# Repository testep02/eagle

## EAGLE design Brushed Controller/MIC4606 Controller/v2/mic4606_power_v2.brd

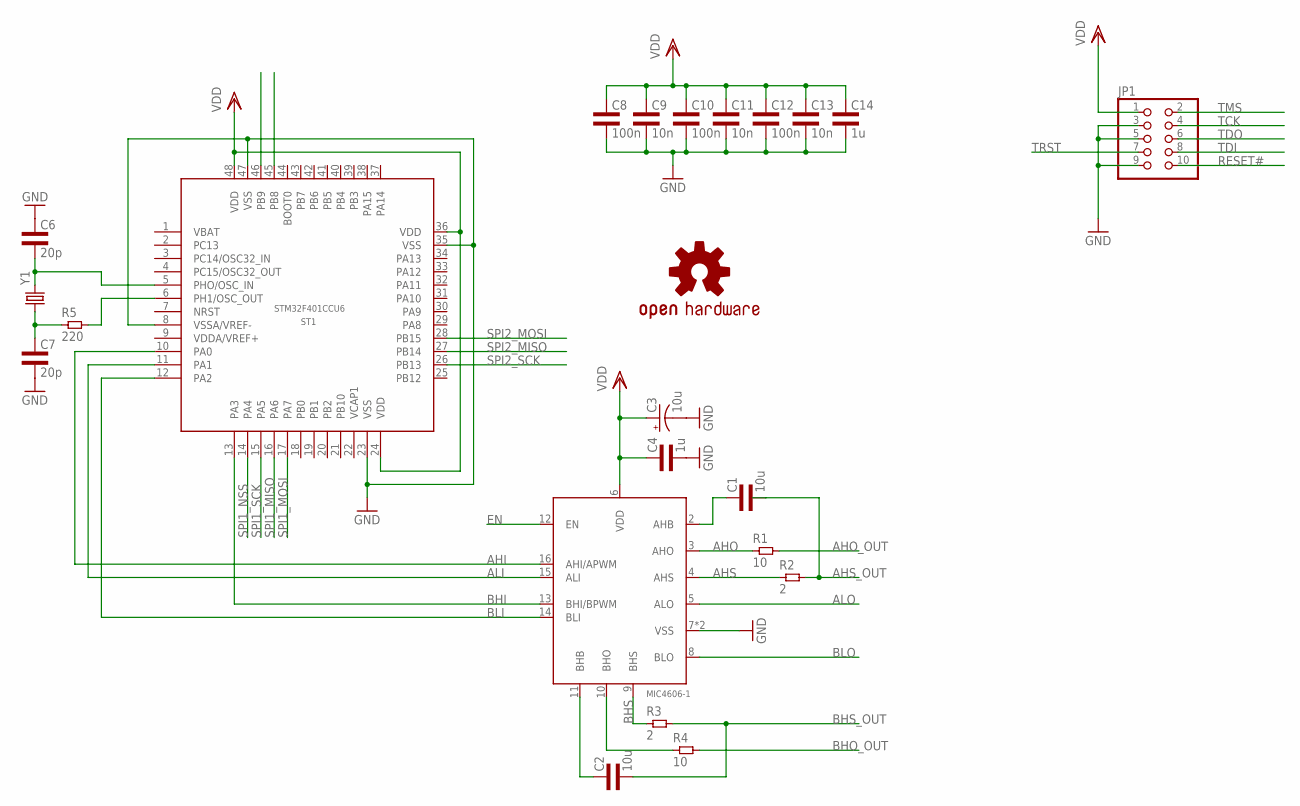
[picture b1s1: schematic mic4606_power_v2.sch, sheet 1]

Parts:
C1, C2: 10u; 0805L3
C3: 10u; E1,8-4
C4: 1u; 0603L3
C6, C7: 20p; 0603L3
C8, C10, C12: 100n; 0603L3
C9, C11, C13: 10n; 0603L3
C14: 1u; 0805L3
JP1: PINHD-2X5; 2X05
LOGO1: OSHW-LOGOM; OSHW-LOGO-M
MD1: MIC4606-1; QFN44-16LD-PL-2
R1, R4: 10; 0805L3
R2, R3: 2; 0805L3
R5: 220; 0603L3
ST1: STM32F401CCU6; UFQFPN48
Y1: CRYSTALHC49US; HC49US

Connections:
AHI: MD1.16 (AHI/APWM), ST1.10 (PA0)
AHO: MD1.3 (AHO), R1.1
AHO_OUT: R1.2
AHS: MD1.4 (AHS), R2.1
AHS_OUT: C1.2, R2.2
ALI: MD1.15 (ALI), ST1.11 (PA1)
ALO: MD1.5 (ALO)
BHI: MD1.13 (BHI/BPWM), ST1.13 (PA3)
BHO: MD1.10 (BHO), R4.1
BHO_OUT: R4.2
BHS: MD1.9 (BHS), R3.1
BHS_OUT: C2.2, R3.2
BLI: MD1.14 (BLI), ST1.12 (PA2)
BLO: MD1.8 (BLO)
CS_G: ST1.45 (PB8); also elsewhere on the board
CS_XM: ST1.46 (PB9); also elsewhere on the board
EN: MD1.12 (EN)
GND: C3.-, C4.P$2 (2), C6.P$1 (1), C7.P$2 (2), C8.P$2 (2), C9.P$2 (2), C10.P$2 (2), C11.P$2 (2), C12.P$2 (2), C13.P$2 (2), C14.2, JP1.3, JP1.5, JP1.9, MD1.7 (VSS), MD1.TP (VSS), ST1.8 (VSSA/VREF-), ST1.23 (VSS), ST1.35 (VSS), ST1.47 (VSS); also elsewhere on the board
unnamed: C1.1, MD1.2 (AHB)
unnamed: R5.P$2 (2), ST1.6 (PH1/OSC_OUT)
unnamed: C7.P$1 (1), R5.P$1 (1), Y1.1
unnamed: C2.1, MD1.11 (BHB)
unnamed: C6.P$2 (2), ST1.5 (PHO/OSC_IN), Y1.2
RESET#: JP1.10
SPI1_MISO: ST1.16 (PA6); also elsewhere on the board
SPI1_MOSI: ST1.17 (PA7); also elsewhere on the board
SPI1_NSS: ST1.14 (PA4); also elsewhere on the board
SPI1_SCK: ST1.15 (PA5); also elsewhere on the board
SPI2_MISO: ST1.27 (PB14); also elsewhere on the board
SPI2_MOSI: ST1.28 (PB15); also elsewhere on the board
SPI2_SCK: ST1.26 (PB13); also elsewhere on the board
TCK: JP1.4
TDI: JP1.8
TDO: JP1.6
TMS: JP1.2
TRST: JP1.7
VDD: C3.+, C4.P$1 (1), C8.P$1 (1), C9.P$1 (1), C10.P$1 (1), C11.P$1 (1), C12.P$1 (1), C13.P$1 (1), C14.1, JP1.1, MD1.6 (VDD), ST1.24 (VDD), ST1.36 (VDD), ST1.48 (VDD); also elsewhere on the board

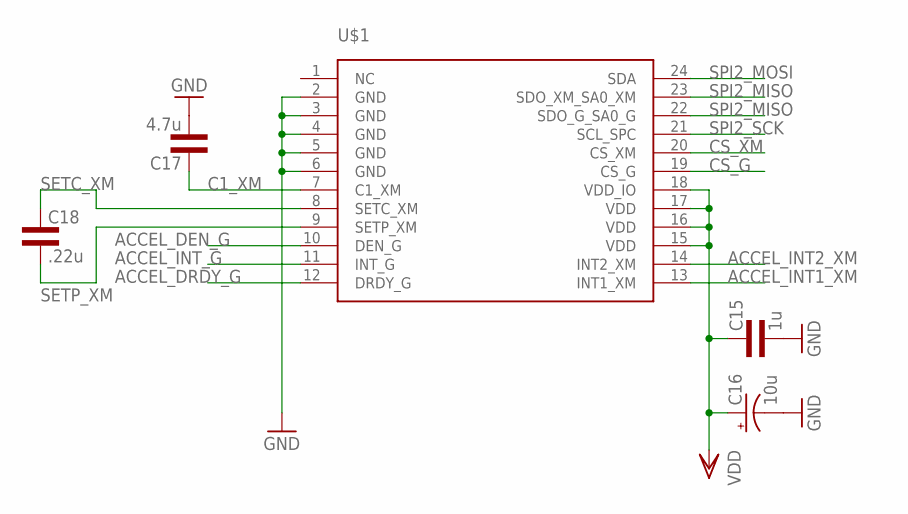
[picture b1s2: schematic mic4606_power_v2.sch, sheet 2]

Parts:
C15: 1u; 0805L3
C16: 10u; CT3216
C17: 4.7u; 0603L3
C18: .22u; 0603L3
U$1: ST_LSM9DS0_TEMP_SENSE_LSM9DS0; ST_LSM9DS0_TEMP_SENSE_LGA-24

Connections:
ACCEL_DEN_G: U$1.10 (DEN_G)
ACCEL_DRDY_G: U$1.12 (DRDY_G)
ACCEL_INT1_XM: U$1.13 (INT1_XM)
ACCEL_INT2_XM: U$1.14 (INT2_XM)
ACCEL_INT_G: U$1.11 (INT_G)
C1_XM: C17.P$1 (1), U$1.7 (C1_XM)
CS_G: U$1.19 (CS_G); also elsewhere on the board
CS_XM: U$1.20 (CS_XM); also elsewhere on the board
GND: C15.2, C16.-, C17.P$2 (2), U$1.2 (GND), U$1.3 (GND), U$1.4 (GND), U$1.5 (GND), U$1.6 (GND); also elsewhere on the board
SETC_XM: C18.P$1 (1), U$1.8 (SETC_XM)
SETP_XM: C18.P$2 (2), U$1.9 (SETP_XM)
SPI2_MISO: U$1.22 (SDO_G_SA0_G), U$1.23 (SDO_XM_SA0_XM); also elsewhere on the board
SPI2_MOSI: U$1.24 (SDA); also elsewhere on the board
SPI2_SCK: U$1.21 (SCL_SPC); also elsewhere on the board
VDD: C15.1, C16.+, U$1.15 (VDD), U$1.16 (VDD), U$1.17 (VDD), U$1.18 (VDD_IO); also elsewhere on the board

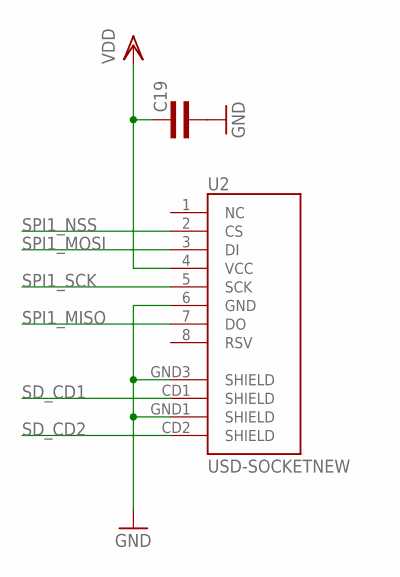
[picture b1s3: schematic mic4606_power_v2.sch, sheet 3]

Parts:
C19: CAP0603L3; 0603L3
U2: USD-SOCKETNEW; MICRO-SD-SOCKET-PP

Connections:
GND: C19.P$2 (2), U2.6 (GND), U2.GND1 (SHIELD), U2.GND3 (SHIELD); also elsewhere on the board
SD_CD1: U2.CD1 (SHIELD)
SD_CD2: U2.CD2 (SHIELD)
SPI1_MISO: U2.7 (DO); also elsewhere on the board
SPI1_MOSI: U2.3 (DI); also elsewhere on the board
SPI1_NSS: U2.2 (CS); also elsewhere on the board
SPI1_SCK: U2.5 (SCK); also elsewhere on the board
VDD: C19.P$1 (1), U2.4 (VCC); also elsewhere on the board

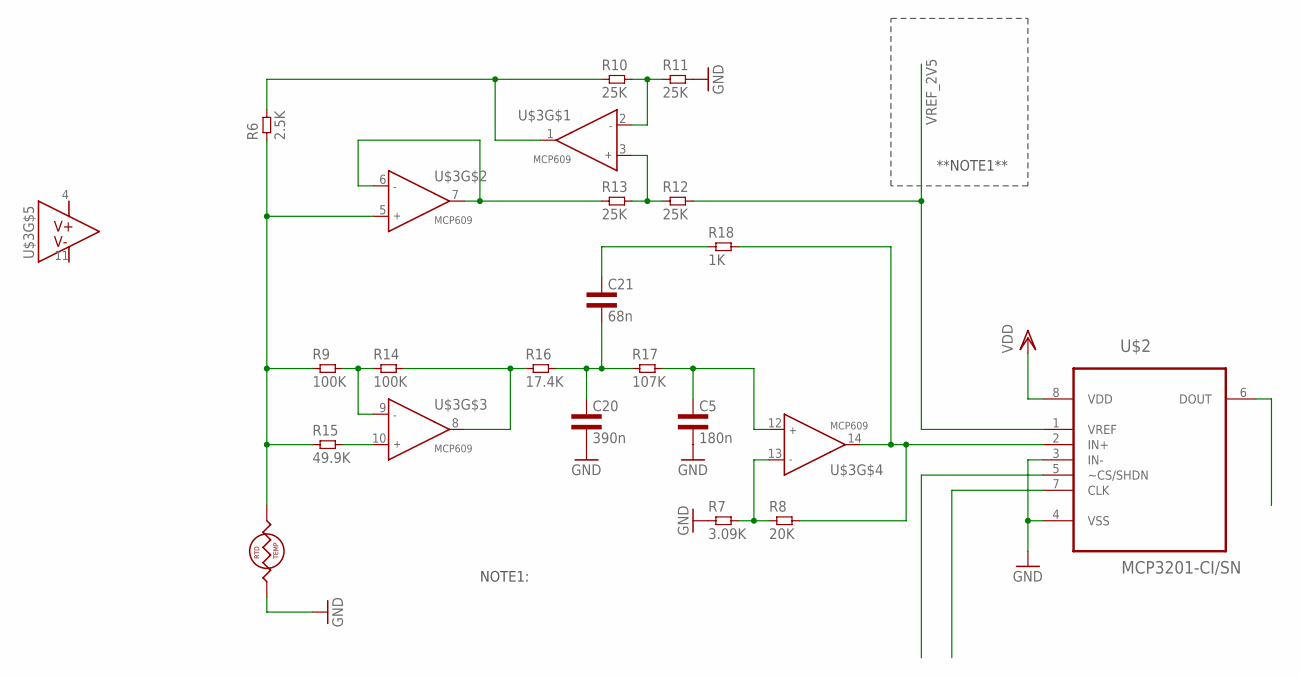
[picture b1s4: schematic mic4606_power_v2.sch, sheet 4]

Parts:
C5: 180n; 0603L3
C20: 390n; 0603L3
C21: 68n; 0603L3
R6: 2.5K; 0603L3
R7: 3.09K; 0603L3
R8: 20K; 0603L3
R9, R14: 100K; 0603L3
R10, R11, R12, R13: 25K; 0603L3
R15: 49.9K; 0603L3
R16: 17.4K; 0603L3
R17: 107K; 0603L3
R18: 1K; 0603L3
RTD1: RTD0805L1; 0805L1
U$2: MCP3201-CI/SN; SOIC127P600X175-8N
U$3: MCP609; TSSOP-14

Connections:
GND: C5.P$2 (2), C20.P$2 (2), R7.P$1 (1), R11.P$2 (2), RTD1.1, U$2.3 (IN-), U$2.4 (VSS); also elsewhere on the board
unnamed: R12.P$1 (1), R13.P$2 (2), U$3.3 (INA+)
unnamed: R10.P$2 (2), R11.P$1 (1), U$3.2 (INA-)
unnamed: R13.P$1 (1), U$3.6 (INA-), U$3.7 (OUTA)
unnamed: R8.P$2 (2), R18.P$2 (2), U$2.2 (IN+), U$3.14 (OUTA)
unnamed: R6.P$2 (2), R10.P$1 (1), U$3.1 (OUTA)
unnamed: R6.P$1 (1), R9.P$1 (1), R15.P$1 (1), RTD1.2, U$3.5 (INA+)
unnamed: R7.P$2 (2), R8.P$1 (1), U$3.13 (INA-)
unnamed: R9.P$2 (2), R14.P$1 (1), U$3.9 (INA-)
unnamed: R15.P$2 (2), U$3.10 (INA+)
unnamed: R14.P$2 (2), R16.P$1 (1), U$3.8 (OUTA)
unnamed: C20.P$1 (1), C21.P$2 (2), R16.P$2 (2), R17.P$1 (1)
unnamed: C5.P$1 (1), R17.P$2 (2), U$3.12 (INA+)
unnamed: C21.P$1 (1), R18.P$1 (1)
V+: U$3.4 (V+)
V-: U$3.11 (V-)
VDD: U$2.8 (VDD); also elsewhere on the board
VREF_2V5: R12.P$2 (2), U$2.1 (VREF)

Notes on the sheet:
**NOTE1**
NOTE1:

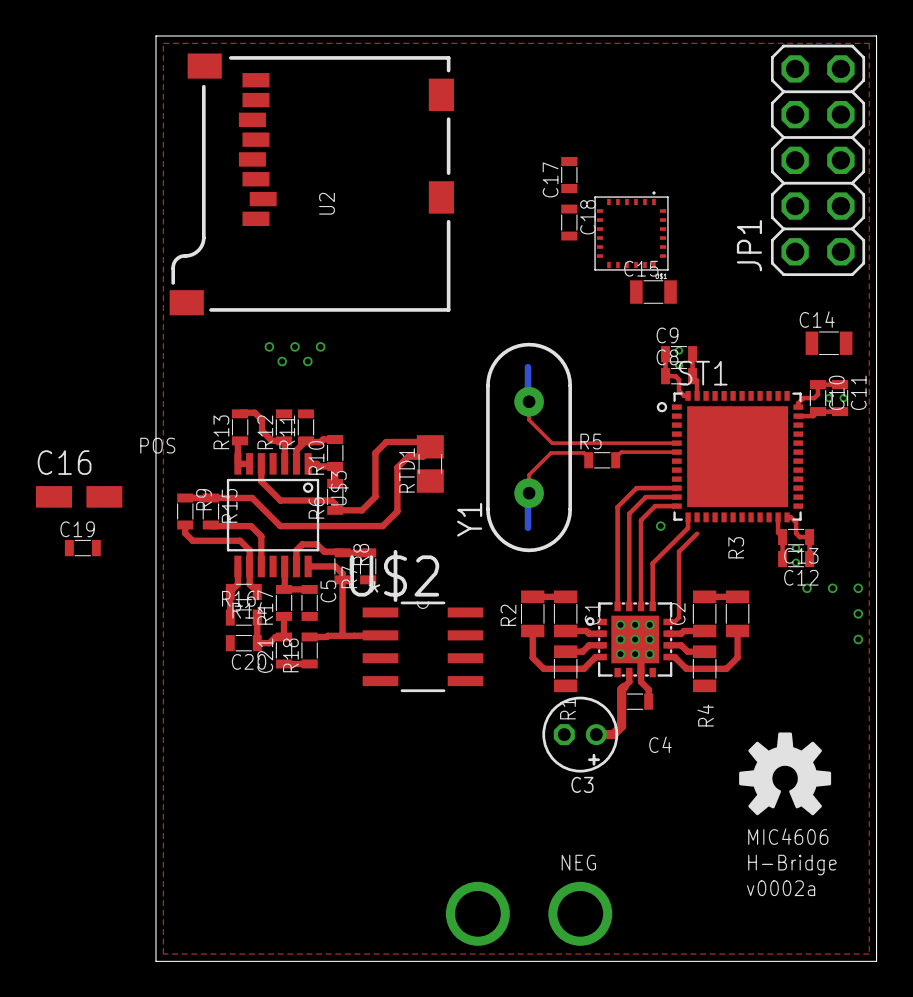
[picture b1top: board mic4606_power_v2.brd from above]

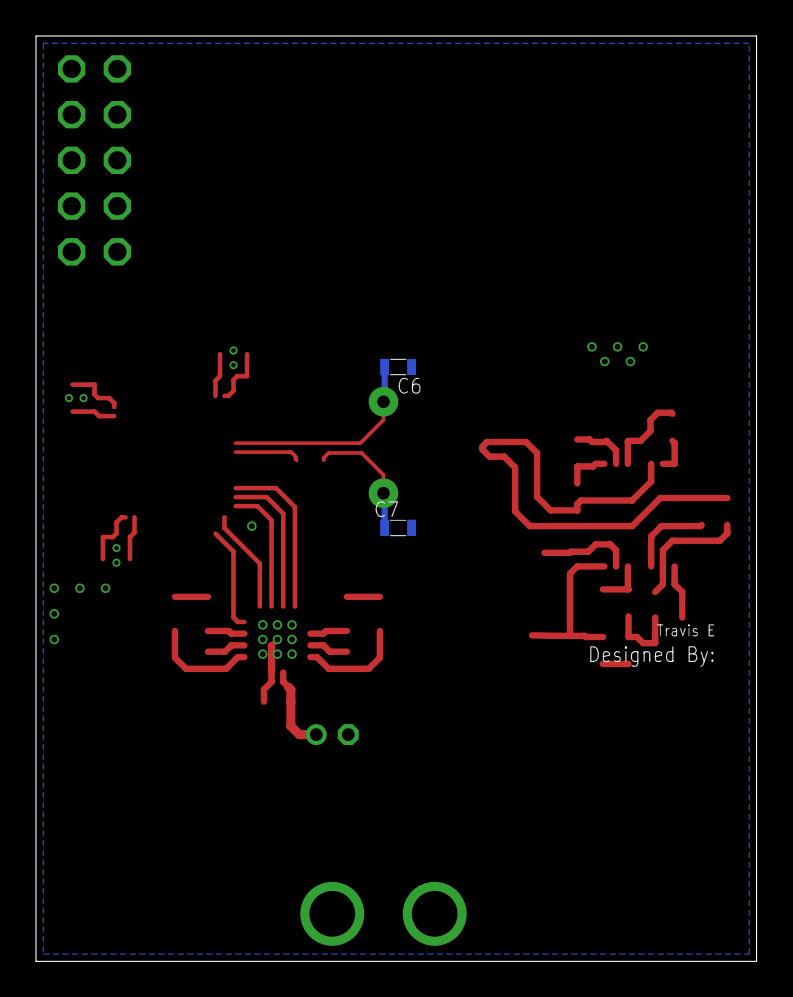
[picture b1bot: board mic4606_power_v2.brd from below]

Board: 2 copper layers, 40.0 x 51.4 mm, 49 parts (2 on the bottom side), 43 nets.

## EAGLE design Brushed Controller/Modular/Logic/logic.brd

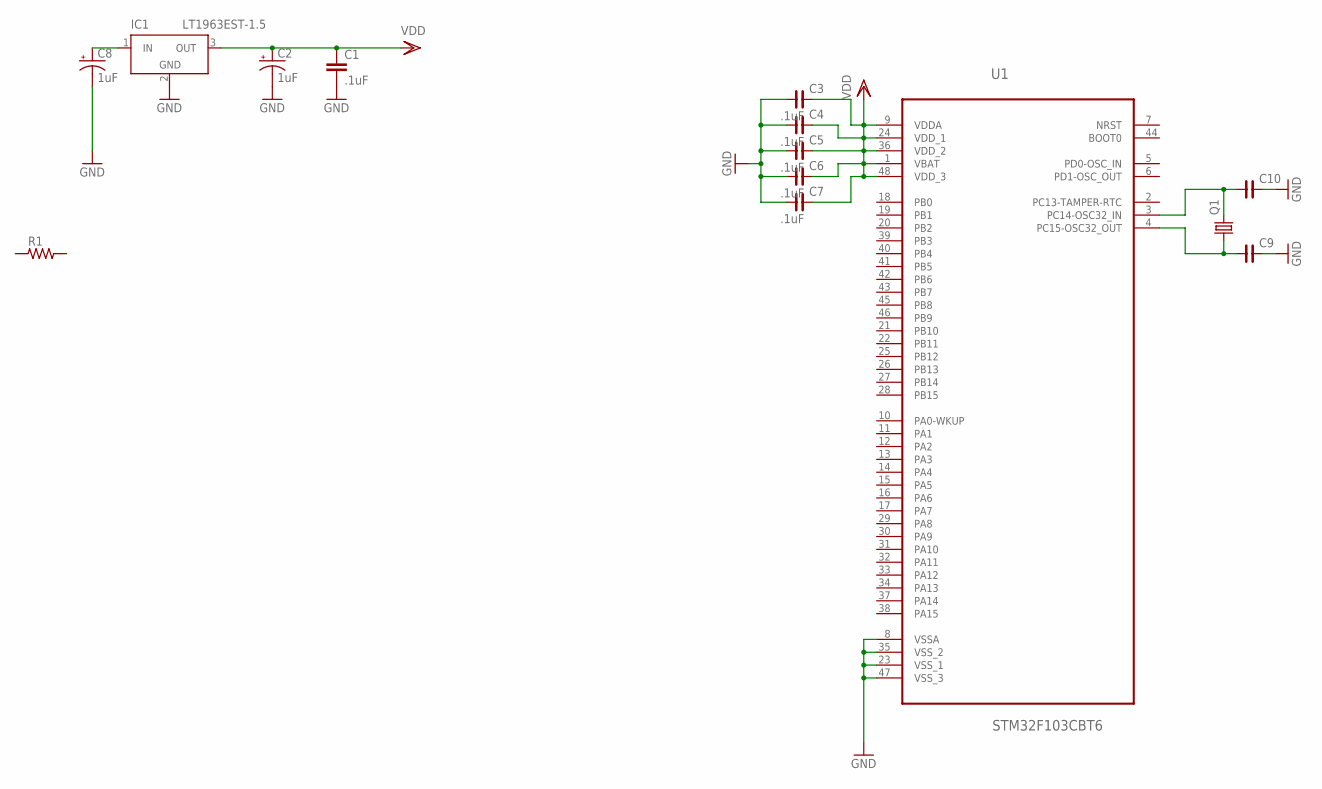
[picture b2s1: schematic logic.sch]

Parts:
C1: .1uF; C0603
C2, C8: 1uF; D/7343-31R
C3, C4, C5, C6, C7: .1uF; C0402
C9, C10: C_0402; C0402
IC1: LT1963EST-1.5; SOT223
Q1: CRYSTALTC26H; TC26H
R1: R_0402; R0402
U1: STM32F103CBT6; QFP50P900X900X160-48N

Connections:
GND: C1.2, C2.-, C3.1, C4.1, C5.1, C6.1, C7.1, C8.-, C9.2, C10.2, IC1.2 (GND), IC1.4 (GND), U1.8 (VSSA), U1.23 (VSS_1), U1.35 (VSS_2), U1.47 (VSS_3)
unnamed: C10.1, Q1.2, U1.3 (PC14-OSC32_IN)
unnamed: C9.1, Q1.1, U1.4 (PC15-OSC32_OUT)
unnamed: C8.+, IC1.1 (IN)
PA11: U1.32 (PA11)
VDD: C1.1, C2.+, C3.2, C4.2, C5.2, C6.2, C7.2, IC1.3 (OUT), U1.1 (VBAT), U1.9 (VDDA), U1.24 (VDD_1), U1.36 (VDD_2), U1.48 (VDD_3)

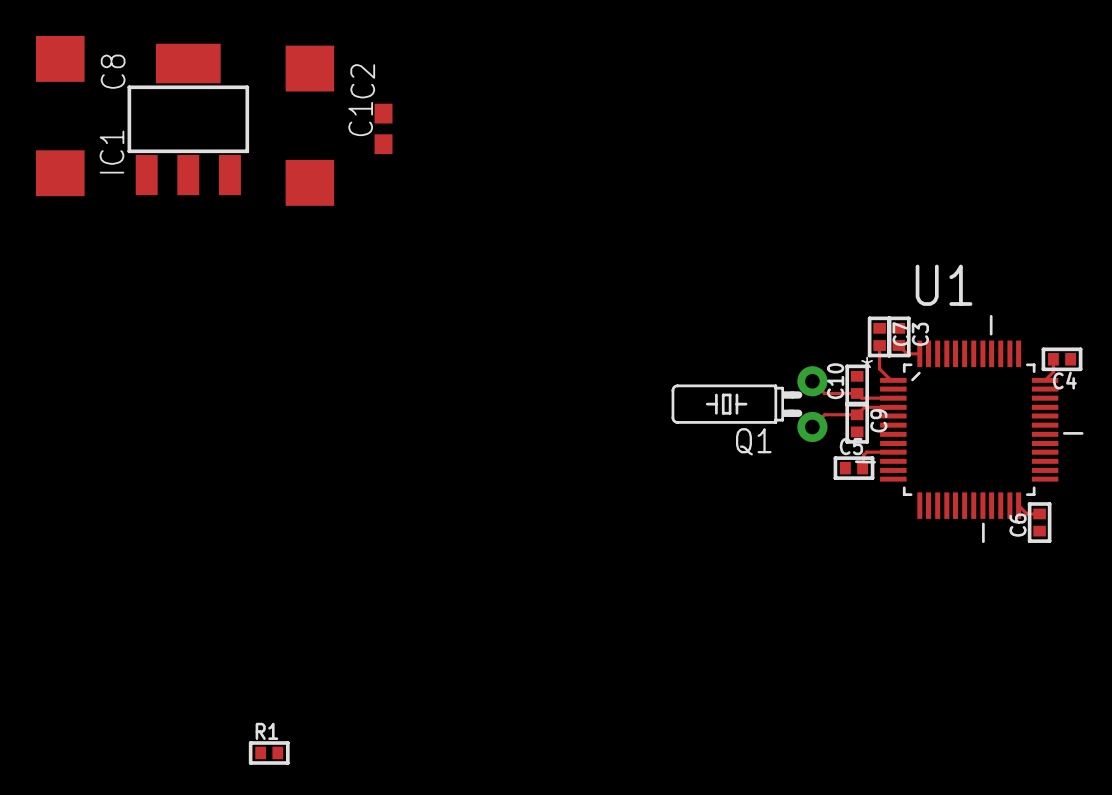
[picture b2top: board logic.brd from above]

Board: 2 copper layers, 14 parts (0 on the bottom side), 5 nets.

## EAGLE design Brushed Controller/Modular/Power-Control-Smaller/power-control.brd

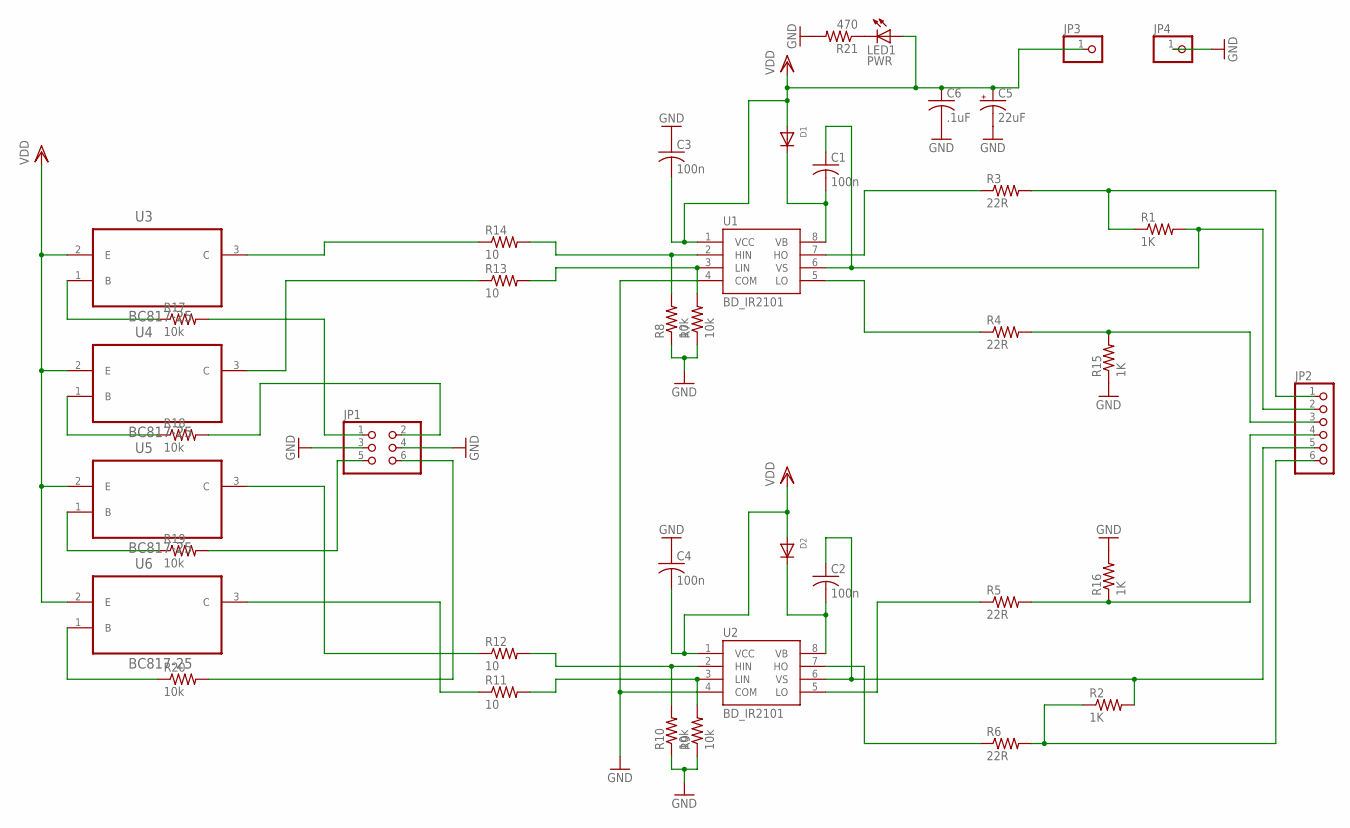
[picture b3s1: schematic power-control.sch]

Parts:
C1, C2, C3, C4: 100n; C0402
C5: 22uF; B/3528-21W
C6: .1uF; C0805
D1, D2: DIODESOD-523; SOD-523
JP1: PINHD-2X3; 2X03
JP2: PINHD-1X6; 1X06
JP3, JP4: PINHD-1X1; 1X01
LED1: PWR; CHIP-LED0805
R1, R2, R15, R16: 1K; R0201
R3, R4, R5, R6: 22R; R0201
R7, R8, R9, R10, R17, R18, R19, R20: 10k; R0201
R11, R12, R13, R14: 10; R0201
R21: 470; R0201
U1, U2: BD_IR2101; SO8
U3, U4, U5, U6: BC817-25; SOT95P240X97-3N

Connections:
GND: C3.1, C4.1, C5.-, C6.2, JP1.3, JP1.4, JP4.1, R7.1, R8.1, R9.1, R10.1, R15.1, R16.2, R21.2, U1.4 (COM), U2.4 (COM)
HO_1: R3.1, U1.7 (HO)
HO_2: R6.1, U2.7 (HO)
LO_1: R4.1, U1.5 (LO)
LO_2: R5.1, U2.5 (LO)
MOTOR_OUT_1: C1.1, JP2.2, R1.2, U1.6 (VS)
MOTOR_OUT_2: C2.1, JP2.5, R2.2, U2.6 (VS)
unnamed: R13.1, U4.3 (C)
unnamed: R11.1, U6.3 (C)
unnamed: R8.2, R14.2, U1.2 (HIN)
unnamed: R7.2, R13.2, U1.3 (LIN)
unnamed: R10.2, R12.2, U2.2 (HIN)
unnamed: R9.2, R11.2, U2.3 (LIN)
unnamed: C1.2, D1.K (C), U1.8 (VB)
unnamed: C2.2, D2.K (C), U2.8 (VB)
unnamed: R12.1, U5.3 (C)
unnamed: JP2.4, R5.2, R16.1
unnamed: R14.1, U3.3 (C)
unnamed: JP1.1, R17.2
unnamed: JP1.5, R19.2
unnamed: JP1.2, R18.2
unnamed: JP2.1, R1.1, R3.2
unnamed: JP1.6, R20.2
unnamed: R17.1, U3.1 (B)
unnamed: R18.1, U4.1 (B)
unnamed: R19.1, U5.1 (B)
unnamed: JP2.3, R4.2, R15.2
unnamed: R20.1, U6.1 (B)
unnamed: LED1.C, R21.1
unnamed: JP2.6, R2.1, R6.2
VDD: C3.2, C4.2, C5.+, C6.1, D1.A, D2.A, JP3.1, LED1.A, U1.1 (VCC), U2.1 (VCC), U3.2 (E), U4.2 (E), U5.2 (E), U6.2 (E)

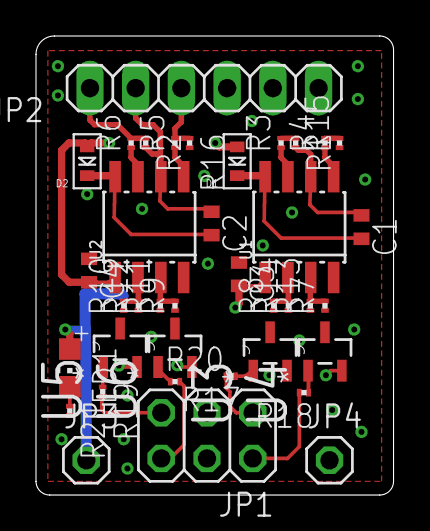
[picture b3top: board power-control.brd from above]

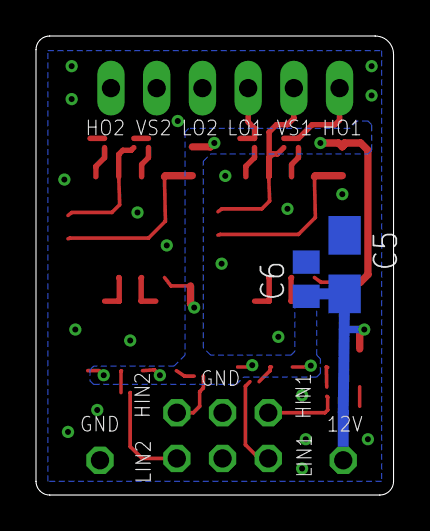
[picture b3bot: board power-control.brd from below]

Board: 2 copper layers, 19.9 x 25.5 mm, 40 parts (2 on the bottom side), 31 nets.

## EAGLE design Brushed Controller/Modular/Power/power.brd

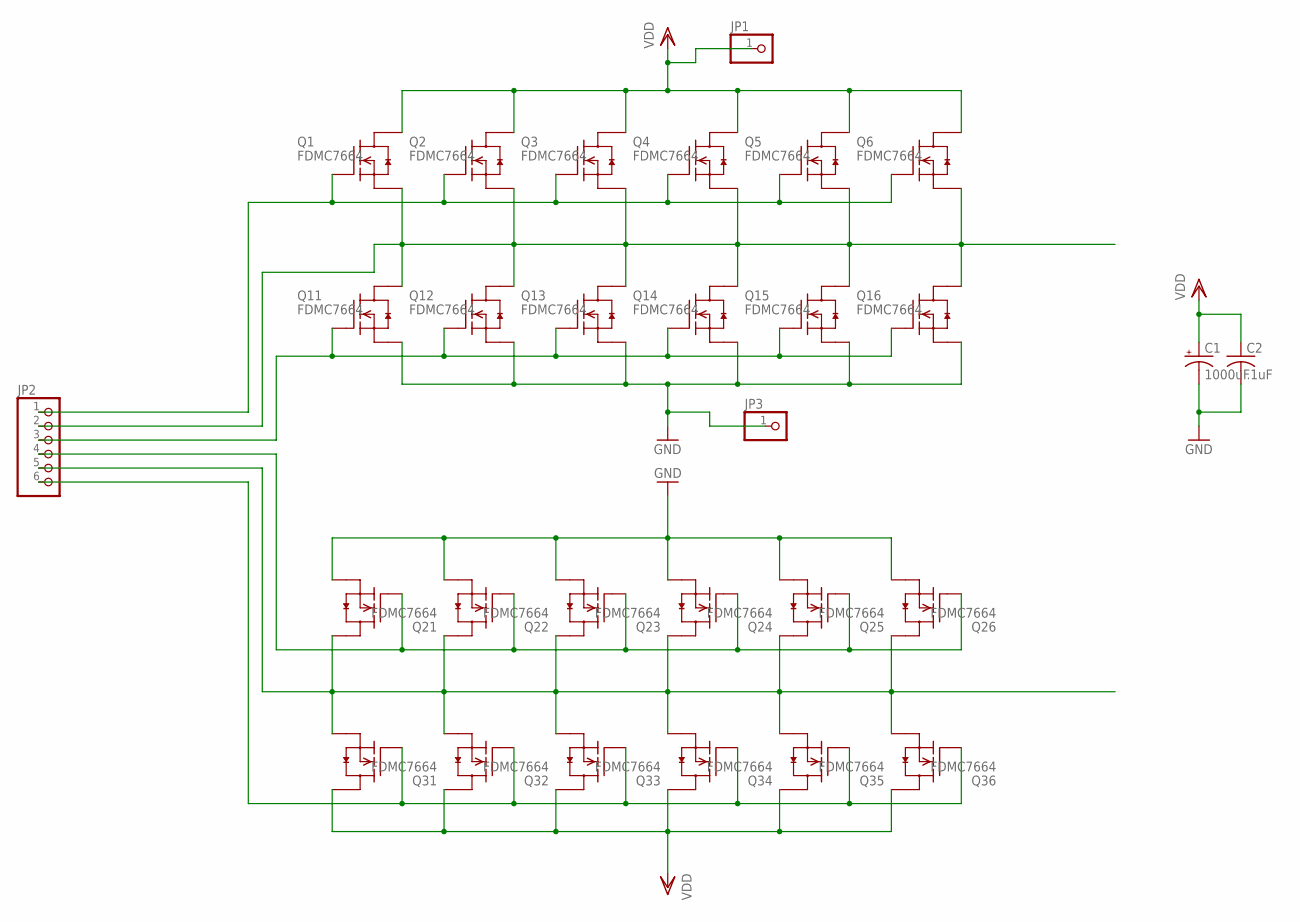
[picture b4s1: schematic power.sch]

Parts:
C1: 1000uF; 140CLH-0810
C2: .1uF; C0603
JP1, JP3: PINHD-1X1; 1X01
JP2: PINHD-1X6; 1X06
Q1, Q2, Q3, Q4, Q5, Q6, Q11, Q12, Q13, Q14, Q15, Q16, Q21, Q22, Q23, Q24, Q25, Q26, Q31, Q32, Q33, Q34, Q35, Q36: FDMC7664; MLP33

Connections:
GND: C1.-, C2.2, JP3.1, Q11.123S (S), Q12.123S (S), Q13.123S (S), Q14.123S (S), Q15.123S (S), Q16.123S (S), Q21.123S (S), Q22.123S (S), Q23.123S (S), Q24.123S (S), Q25.123S (S), Q26.123S (S)
HO_1: JP2.1, Q1.4G (G), Q2.4G (G), Q3.4G (G), Q4.4G (G), Q5.4G (G), Q6.4G (G)
HO_2: JP2.6, Q31.4G (G), Q32.4G (G), Q33.4G (G), Q34.4G (G), Q35.4G (G), Q36.4G (G)
LO_1: JP2.3, Q11.4G (G), Q12.4G (G), Q13.4G (G), Q14.4G (G), Q15.4G (G), Q16.4G (G)
LO_2: JP2.4, Q21.4G (G), Q22.4G (G), Q23.4G (G), Q24.4G (G), Q25.4G (G), Q26.4G (G)
MOTOR_OUT_1: JP2.2, Q1.123S (S), Q2.123S (S), Q3.123S (S), Q4.123S (S), Q5.123S (S), Q6.123S (S), Q11.5678D (D), Q12.5678D (D), Q13.5678D (D), Q14.5678D (D), Q15.5678D (D), Q16.5678D (D)
MOTOR_OUT_2: JP2.5, Q21.5678D (D), Q22.5678D (D), Q23.5678D (D), Q24.5678D (D), Q25.5678D (D), Q26.5678D (D), Q31.123S (S), Q32.123S (S), Q33.123S (S), Q34.123S (S), Q35.123S (S), Q36.123S (S)
VDD: C1.+, C2.1, JP1.1, Q1.5678D (D), Q2.5678D (D), Q3.5678D (D), Q4.5678D (D), Q5.5678D (D), Q6.5678D (D), Q31.5678D (D), Q32.5678D (D), Q33.5678D (D), Q34.5678D (D), Q35.5678D (D), Q36.5678D (D)

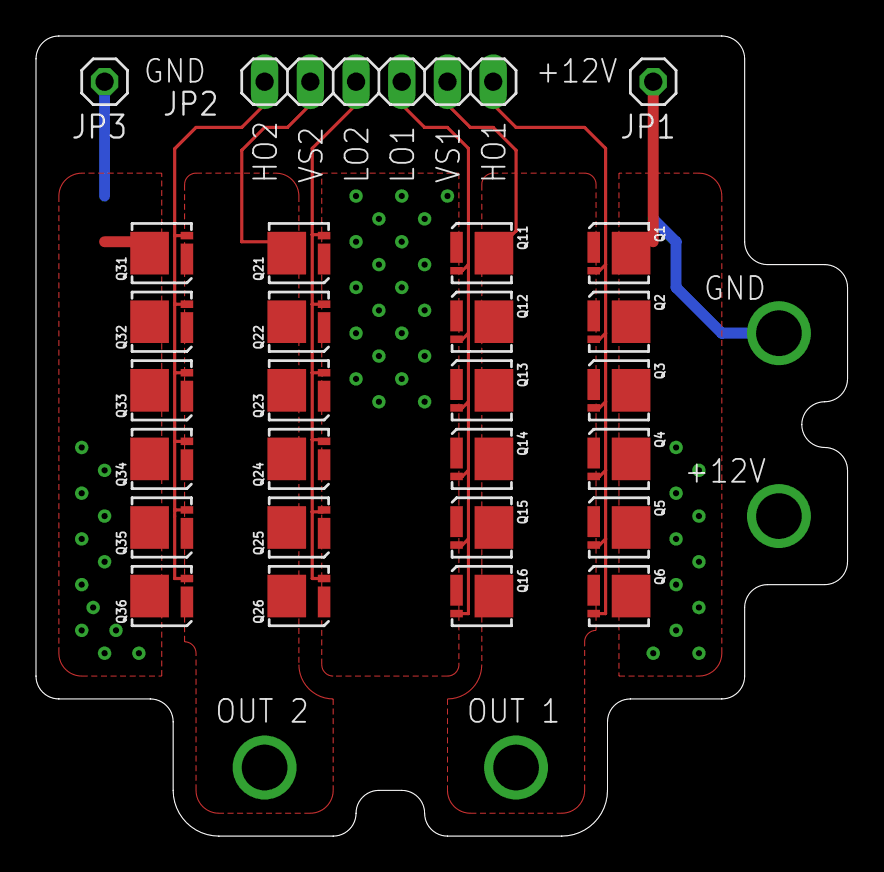
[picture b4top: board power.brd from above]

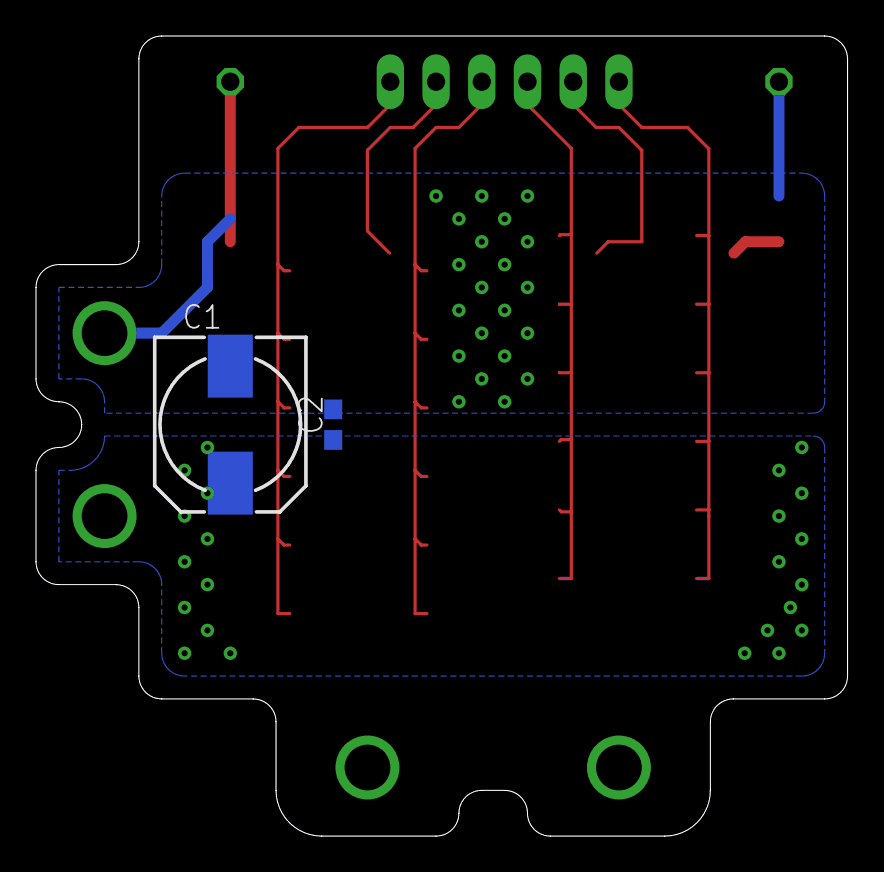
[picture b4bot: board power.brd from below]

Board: 2 copper layers, 45.1 x 44.4 mm, 29 parts (2 on the bottom side), 8 nets.

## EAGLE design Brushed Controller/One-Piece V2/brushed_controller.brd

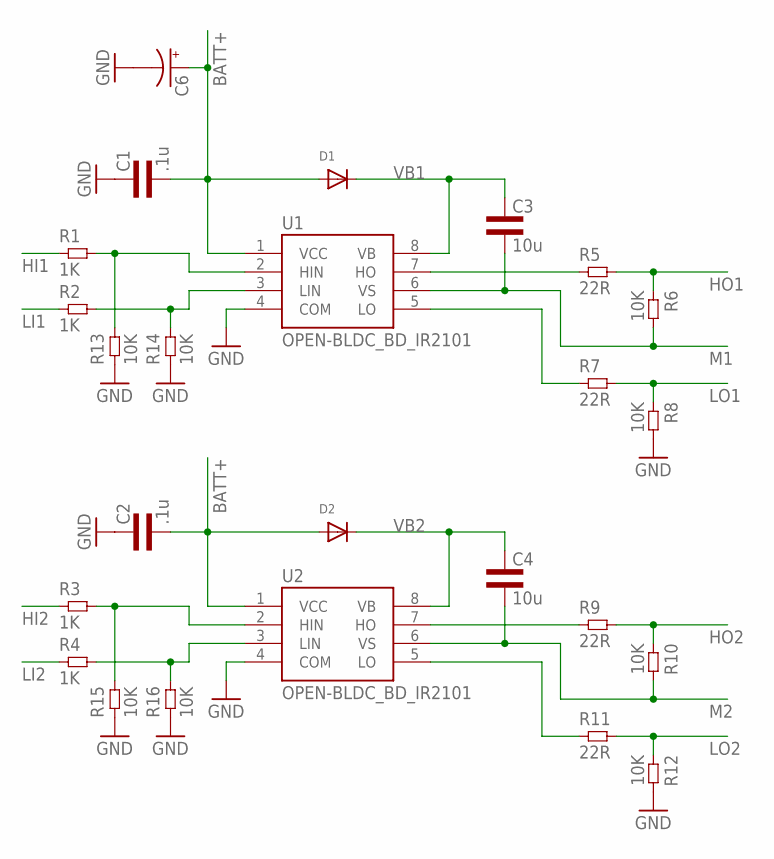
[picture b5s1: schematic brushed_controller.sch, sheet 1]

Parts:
C1, C2: .1u; 0603L3
C3, C4: 10u; 0805L3
C6: CPOL-USCT7343; CT7343
D1, D2: DIODESOD-523; SOD-523
R1, R2, R3, R4: 1K; 0603L3
R5, R7, R9, R11: 22R; 0805L3
R6, R8, R10, R12: 10K; 0805L3
R13, R14, R15, R16: 10K; 0603L3
U1, U2: OPEN-BLDC_BD_IR2101; OPEN-BLDC_SO8

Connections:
BATT+: C1.P$2 (2), C2.P$2 (2), C6.+, D1.A, D2.A, U1.1 (VCC), U2.1 (VCC); also elsewhere on the board
GND: C1.P$1 (1), C2.P$1 (1), C6.-, R8.2, R12.2, R13.P$1 (1), R14.P$1 (1), R15.P$1 (1), R16.P$1 (1), U1.4 (COM), U2.4 (COM); also elsewhere on the board
H1: R5.1, U1.7 (HO)
H2: R9.1, U2.7 (HO)
HI1: R1.P$1 (1)
HI2: R3.P$1 (1)
HO1: R5.2, R6.1; also elsewhere on the board
HO2: R9.2, R10.1
L1: R7.1, U1.5 (LO)
L2: R11.1, U2.5 (LO)
LI1: R2.P$1 (1)
LI2: R4.P$1 (1)
LO1: R7.2, R8.1; also elsewhere on the board
LO2: R11.2, R12.1; also elsewhere on the board
M1: C3.2, R6.2, U1.6 (VS); also elsewhere on the board
M2: C4.2, R10.2, U2.6 (VS); also elsewhere on the board
unnamed: R1.P$2 (2), R13.P$2 (2), U1.2 (HIN)
unnamed: R2.P$2 (2), R14.P$2 (2), U1.3 (LIN)
unnamed: R3.P$2 (2), R15.P$2 (2), U2.2 (HIN)
unnamed: R4.P$2 (2), R16.P$2 (2), U2.3 (LIN)
VB1: C3.1, D1.K (C), U1.8 (VB)
VB2: C4.1, D2.K (C), U2.8 (VB)

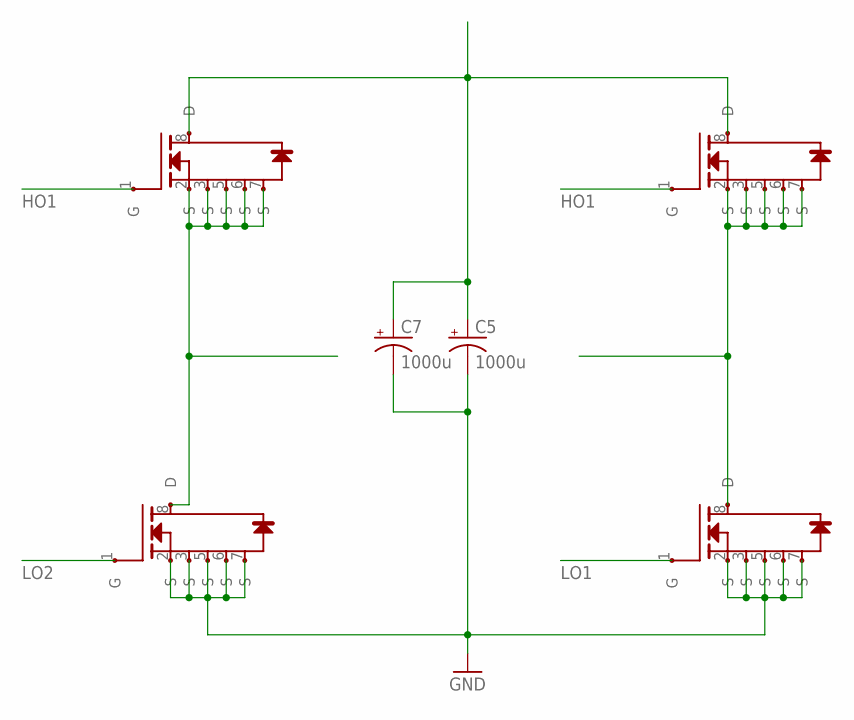
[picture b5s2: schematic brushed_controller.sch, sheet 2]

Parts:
C5, C7: 1000u; E5-13
U$1, U$2, U$3, U$4: IR-MOSFETS_IRF3805STRL-7PP; IR-MOSFETS_D2PAK-7

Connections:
BATT+: C5.+, C7.+, U$1.8 (D), U$3.8 (D); also elsewhere on the board
GND: C5.-, C7.-, U$2.2 (S), U$2.3 (S), U$2.5 (S), U$2.6 (S), U$2.7 (S), U$4.2 (S), U$4.3 (S), U$4.5 (S), U$4.6 (S), U$4.7 (S); also elsewhere on the board
HO1: U$1.1 (G), U$3.1 (G); also elsewhere on the board
LO1: U$4.1 (G); also elsewhere on the board
LO2: U$2.1 (G); also elsewhere on the board
M1: U$1.2 (S), U$1.3 (S), U$1.5 (S), U$1.6 (S), U$1.7 (S), U$2.8 (D); also elsewhere on the board
M2: U$3.2 (S), U$3.3 (S), U$3.5 (S), U$3.6 (S), U$3.7 (S), U$4.8 (D); also elsewhere on the board

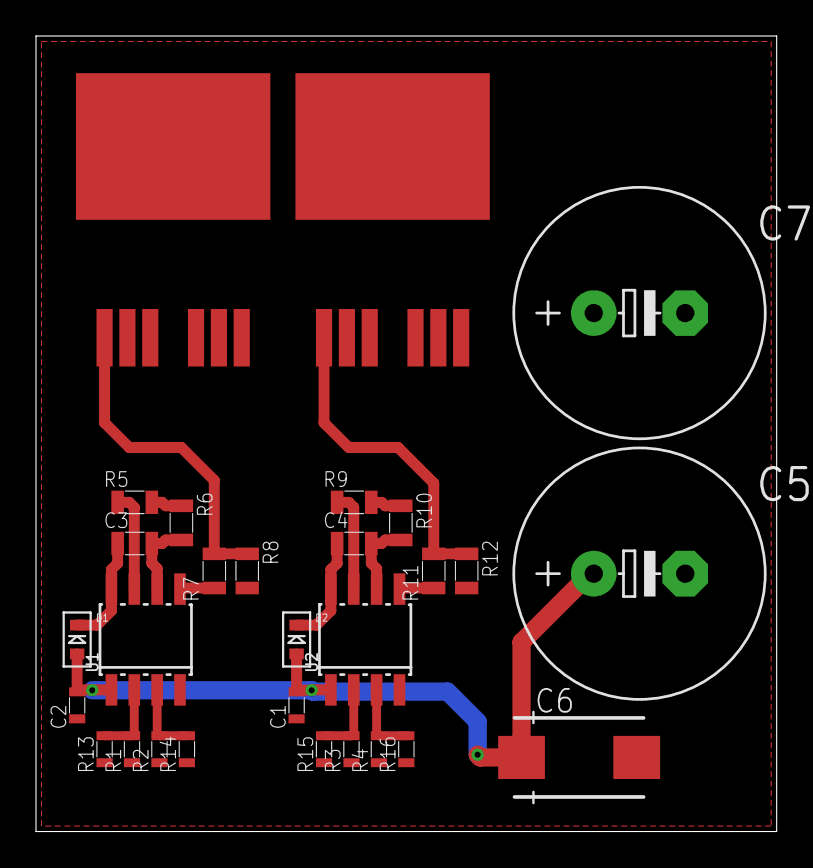
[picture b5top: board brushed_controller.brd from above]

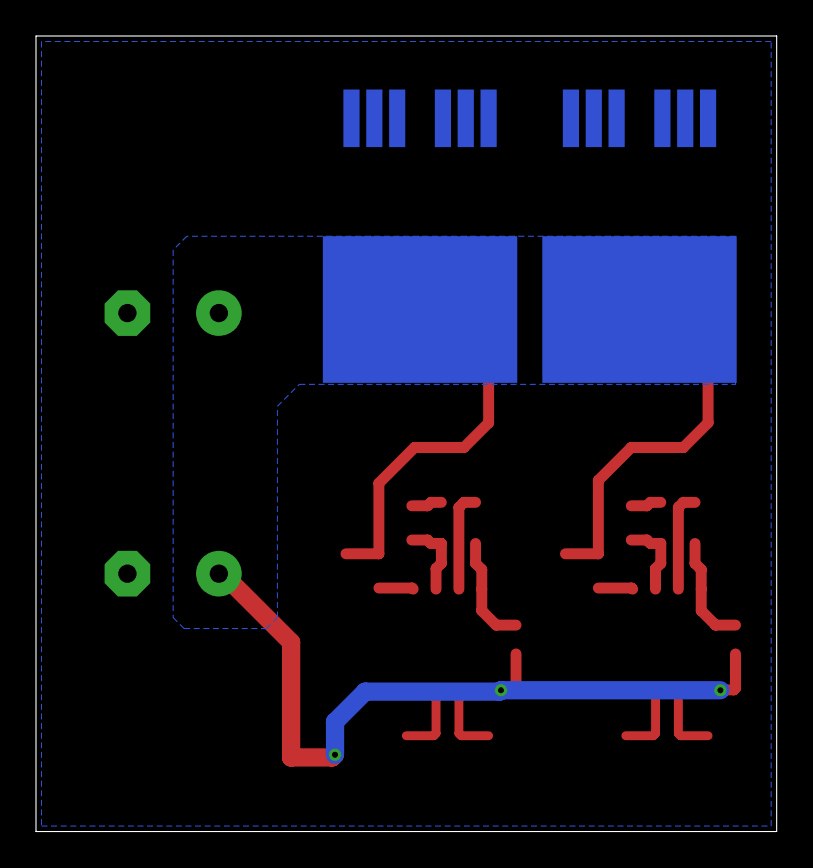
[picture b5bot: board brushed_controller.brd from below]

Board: 2 copper layers, 41.1 x 44.2 mm, 31 parts (2 on the bottom side), 18 nets.

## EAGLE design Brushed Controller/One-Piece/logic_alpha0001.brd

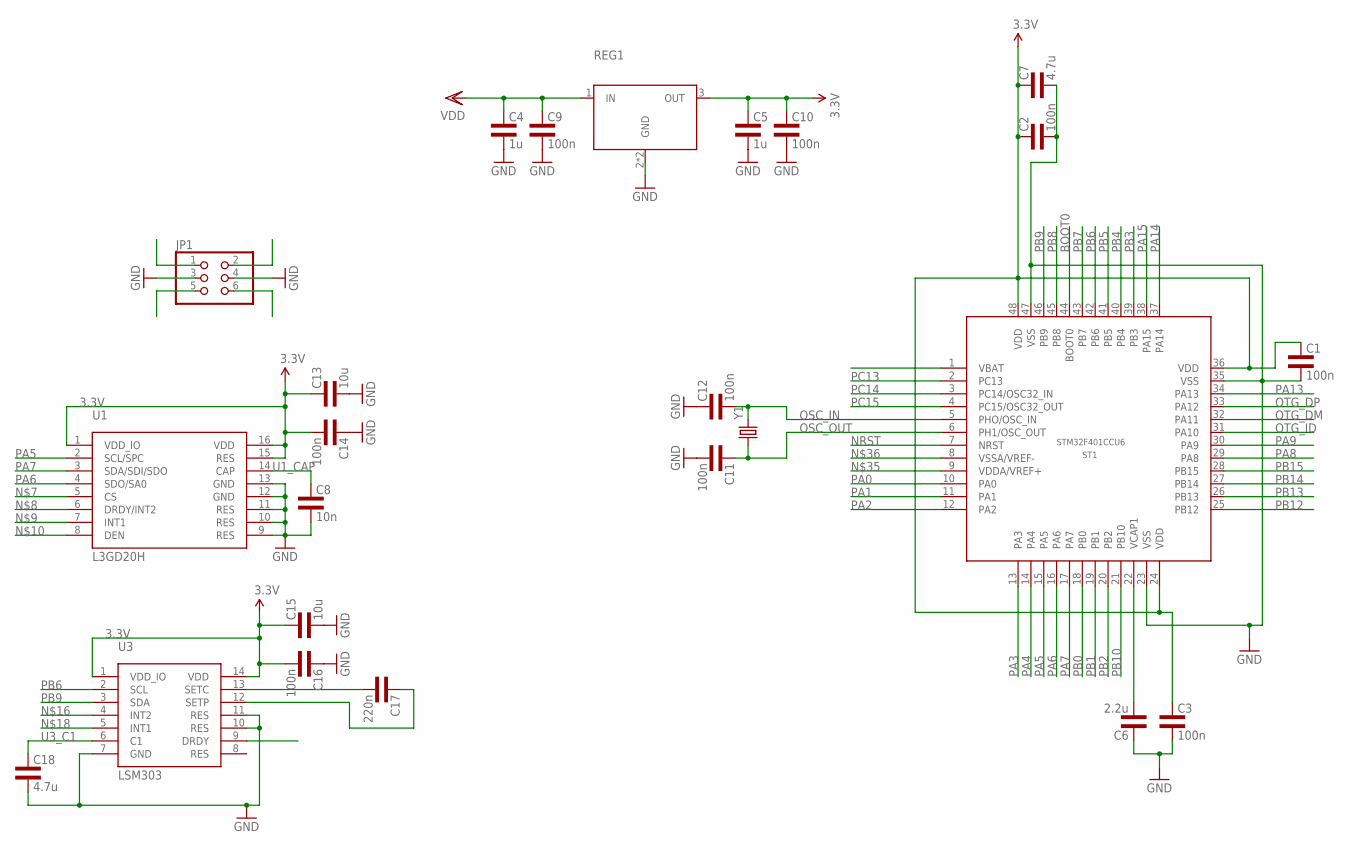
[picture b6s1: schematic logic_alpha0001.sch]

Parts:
C1, C2, C3, C11, C12: 100n; 0402L3
C4, C5: 1u; 0805L3
C6: 2.2u; 0402L3
C7: 4.7u; 0805L3
C8: 10n; 0603L3
C9, C10, C14, C16: 100n; 0603L3
C13, C15: 10u; 0805L3
C17: 220n; 0603L3
C18: 4.7u; 0603L3
JP1: PINHD-2X3; 2X03
REG1: LDO_REG_4PIN; SOT-223-3
ST1: STM32F401CCU6; UFQFPN48
U1: L3GD20H; LGA16R50P3X5_300X300X100
U3: LSM303; LGA14
Y1: CRYSTALHC49US; HC49US

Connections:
3.3V: C1.P$1 (1), C2.P$1 (1), C3.P$1 (1), C5.1, C7.1, C10.P$1 (1), C13.1, C14.P$2 (2), C15.1, C16.P$2 (2), REG1.3 (OUT), ST1.24 (VDD), ST1.36 (VDD), ST1.48 (VDD), U1.1 (VDD_IO), U1.15 (RES), U1.16 (VDD), U3.1 (VDD_IO), U3.14 (VDD)
BOOT0: ST1.44 (BOOT0)
GND: C1.P$2 (2), C2.P$2 (2), C3.P$2 (2), C4.2, C5.2, C6.P$1 (1), C7.2, C8.P$2 (2), C9.P$2 (2), C10.P$2 (2), C11.P$2 (2), C12.P$1 (1), C13.2, C14.P$1 (1), C15.2, C16.P$1 (1), C18.P$2 (2), JP1.3, JP1.4, REG1.2 (GND), REG1.4 (GND), ST1.23 (VSS), ST1.35 (VSS), ST1.47 (VSS), U1.9 (RES), U1.10 (RES), U1.11 (RES), U1.12 (GND), U1.13 (GND), U3.7 (GND), U3.10 (RES), U3.11 (RES)
HIN1_IN: JP1.1
HIN2_IN: JP1.5
LIN1_IN: JP1.2
LIN2_IN: JP1.6
unnamed: C6.P$2 (2), ST1.22 (VCAP1)
unnamed: C17.P$2 (2), U3.13 (SETC)
unnamed: C17.P$1 (1), U3.12 (SETP)
NRST: ST1.7 (NRST)
OSC_IN: C12.P$2 (2), ST1.5 (PHO/OSC_IN), Y1.2
OSC_OUT: C11.P$1 (1), ST1.6 (PH1/OSC_OUT), Y1.1
OTG_DM: ST1.32 (PA11)
OTG_DP: ST1.33 (PA12)
OTG_ID: ST1.31 (PA10)
PA0: ST1.10 (PA0)
PA1: ST1.11 (PA1)
PA2: ST1.12 (PA2)
PA3: ST1.13 (PA3)
PA4: ST1.14 (PA4)
PA5: ST1.15 (PA5), U1.2 (SCL/SPC)
PA6: ST1.16 (PA6), U1.4 (SDO/SA0)
PA7: ST1.17 (PA7), U1.3 (SDA/SDI/SDO)
PA8: ST1.29 (PA8)
PA9: ST1.30 (PA9)
PA13: ST1.34 (PA13)
PA14: ST1.37 (PA14)
PA15: ST1.38 (PA15)
PB0: ST1.18 (PB0)
PB1: ST1.19 (PB1)
PB2: ST1.20 (PB2)
PB3: ST1.39 (PB3)
PB4: ST1.40 (PB4)
PB5: ST1.41 (PB5)
PB6: ST1.42 (PB6), U3.2 (SCL)
PB7: ST1.43 (PB7)
PB8: ST1.45 (PB8)
PB9: ST1.46 (PB9), U3.3 (SDA)
PB10: ST1.21 (PB10)
PB12: ST1.25 (PB12)
PB13: ST1.26 (PB13)
PB14: ST1.27 (PB14)
PB15: ST1.28 (PB15)
PC13: ST1.2 (PC13)
PC14: ST1.3 (PC14/OSC32_IN)
PC15: ST1.4 (PC15/OSC32_OUT)
U1_CAP: C8.P$1 (1), U1.14 (CAP)
U3_C1: C18.P$1 (1), U3.6 (C1)
VDD: C4.1, C9.P$1 (1), REG1.1 (IN)

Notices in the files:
parts and their libraries:
SparkFun-Aesthetics: Licensing: CC v3.0 Share-Alike You are welcome to use this library for commercial purposes.
rc-master: Copyright (C) 2007, Bob Starr
